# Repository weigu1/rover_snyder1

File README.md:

# Creative-lab space mining rover: Snyder 1

## Some infos

The rover is WLAN controlled by a computer or phone. The new  version uses websockets to controll the rover using sliders.
The rover was developed by Jean Daubenfeld and myself for the [creative-lab](http://creative-lab.lu) and was build 35 times on 2 Luxemburgish Makerfest.

## All infos ESP8266 version : <http://www.weigu.lu/microcontroller/rover/index.html>
## All infos ESP32 version : <http://weigu.lu/tutorials/electronics/01_rover/index.html>

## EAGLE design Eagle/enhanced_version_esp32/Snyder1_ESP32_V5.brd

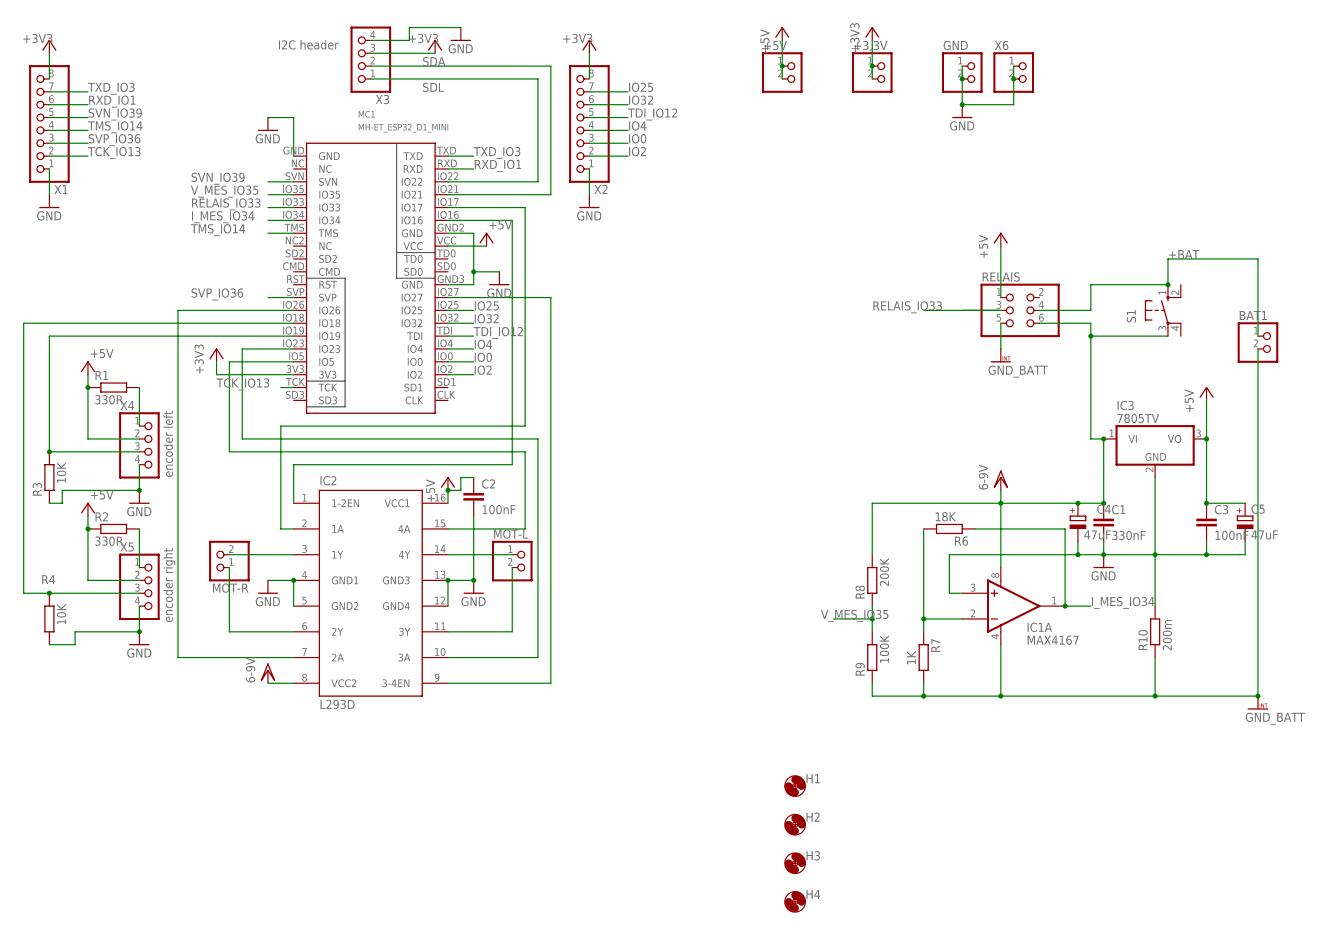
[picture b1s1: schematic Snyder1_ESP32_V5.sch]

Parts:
+3,3V, +5V: PINHD-1X2; 1X02
BAT1: PINHD-1X2; 1X02
C1: 330nF; C050-025X075
C2, C3: 100nF; C050-025X075
C4, C5: 47uF; E2,5-5
GND: PINHD-1X2; 1X02
H1, H2, H3, H4: MOUNT-HOLE3.2; 3,2
IC1: MAX4167; DIL08
IC2: L293D; DIL16
IC3: 7805TV; TO220V
MC1: MH-ET_ESP32_D1_MINI
MOT-L: PINHD-1X2; 1X02
MOT-R: PINHD-1X2; 1X02
R1, R2: 330R; 0207/10
R3, R4: 10K; 0207/10
R6: 18K; 0207/10
R7: 1K; 0207/10
R8: 200K; 0207/10
R9: 100K; 0207/10
R10: 200m; 0411/15
RELAIS: PINHD-2X3; 2X03
S1: 10-XX; B3F-10XX
X1, X2: PINHD-1X8; 1X08
X3: I2C header; 1X04
X4: encoder left; 1X04
X5: encoder right; 1X04
X6: PINHD-1X2; 1X02

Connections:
6-9V: C1.1, C4.+, IC1.8 (V+), IC2.8 (VCC2), IC3.1 (VI), R8.2, RELAIS.6, S1.3
+3V3: +3,3V.1, +3,3V.2, MC1.3V3, X1.8, X2.8, X3.3
+5V: +5V.1, +5V.2, C2.1, C3.1, C5.+, IC2.16 (VCC1), IC3.3 (VO), MC1.VCC, R1.1, R2.1, RELAIS.1, X4.2, X5.2
+BAT: BAT1.1, RELAIS.4, S1.1 (S)
GND: C1.2, C2.2, C3.2, C4.-, C5.-, GND.1, GND.2, IC1.3 (+IN), IC2.4 (GND1), IC2.5 (GND2), IC2.12 (GND4), IC2.13 (GND3), IC3.2 (GND), MC1.GND, MC1.GND2 (GND), MC1.GND3 (GND), R3.1, R4.1, R10.2, X1.1, X2.1, X3.4, X4.4, X5.4, X6.1, X6.2
GNDINT: BAT1.2, IC1.4 (V-), R7.2, R9.1, R10.1, RELAIS.5
IO0: MC1.IO0, X2.3
IO2: MC1.IO2, X2.2
IO4: MC1.IO4, X2.4
IO25: MC1.IO25, X2.7
IO32: MC1.IO32, X2.6
I_MES_IO34: IC1.1 (OUT), MC1.IO34, R6.1
unnamed: IC2.3 (1Y), MOT-R.2
unnamed: IC2.6 (2Y), MOT-R.1
unnamed: IC2.14 (4Y), MOT-L.1
unnamed: IC2.11 (3Y), MOT-L.2
unnamed: IC2.10 (3A), MC1.IO23
unnamed: IC2.15 (4A), MC1.IO5
unnamed: R2.2, X5.1
unnamed: R1.2, X4.1
unnamed: IC2.2 (1A), MC1.IO17
unnamed: MC1.IO19, R3.2, X4.3
unnamed: MC1.IO18, R4.2, X5.3
unnamed: IC2.7 (2A), MC1.IO26
unnamed: IC1.2 (-IN), R6.2, R7.1
unnamed: IC2.1 (1-2EN), MC1.IO16
unnamed: IC2.9 (3-4EN), MC1.IO27
RELAIS_IO33: MC1.IO33, RELAIS.3
RXD_IO1: MC1.RXD, X1.6
SDA: MC1.IO21, X3.2
SDL: MC1.IO22, X3.1
SVN_IO39: MC1.SVN, X1.5
SVP_IO36: MC1.SVP, X1.3
TCK_IO13: MC1.TCK, X1.2
TDI_IO12: MC1.TDI, X2.5
TMS_IO14: MC1.TMS, X1.4
TXD_IO3: MC1.TXD, X1.7
V_MES_IO35: MC1.IO35, R8.1, R9.2

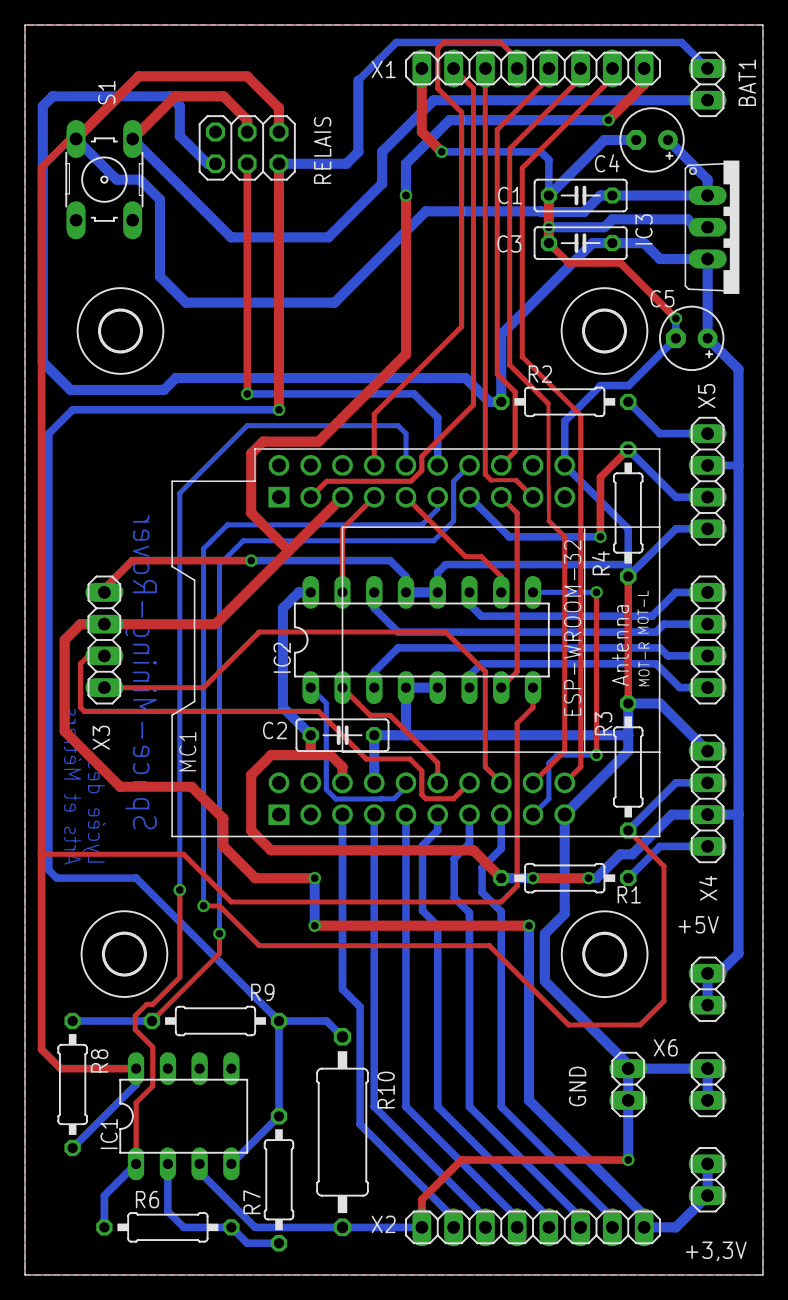
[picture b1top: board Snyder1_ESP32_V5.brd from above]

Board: 2 copper layers, 59.0 x 100.0 mm, 36 parts (0 on the bottom side), 38 nets.

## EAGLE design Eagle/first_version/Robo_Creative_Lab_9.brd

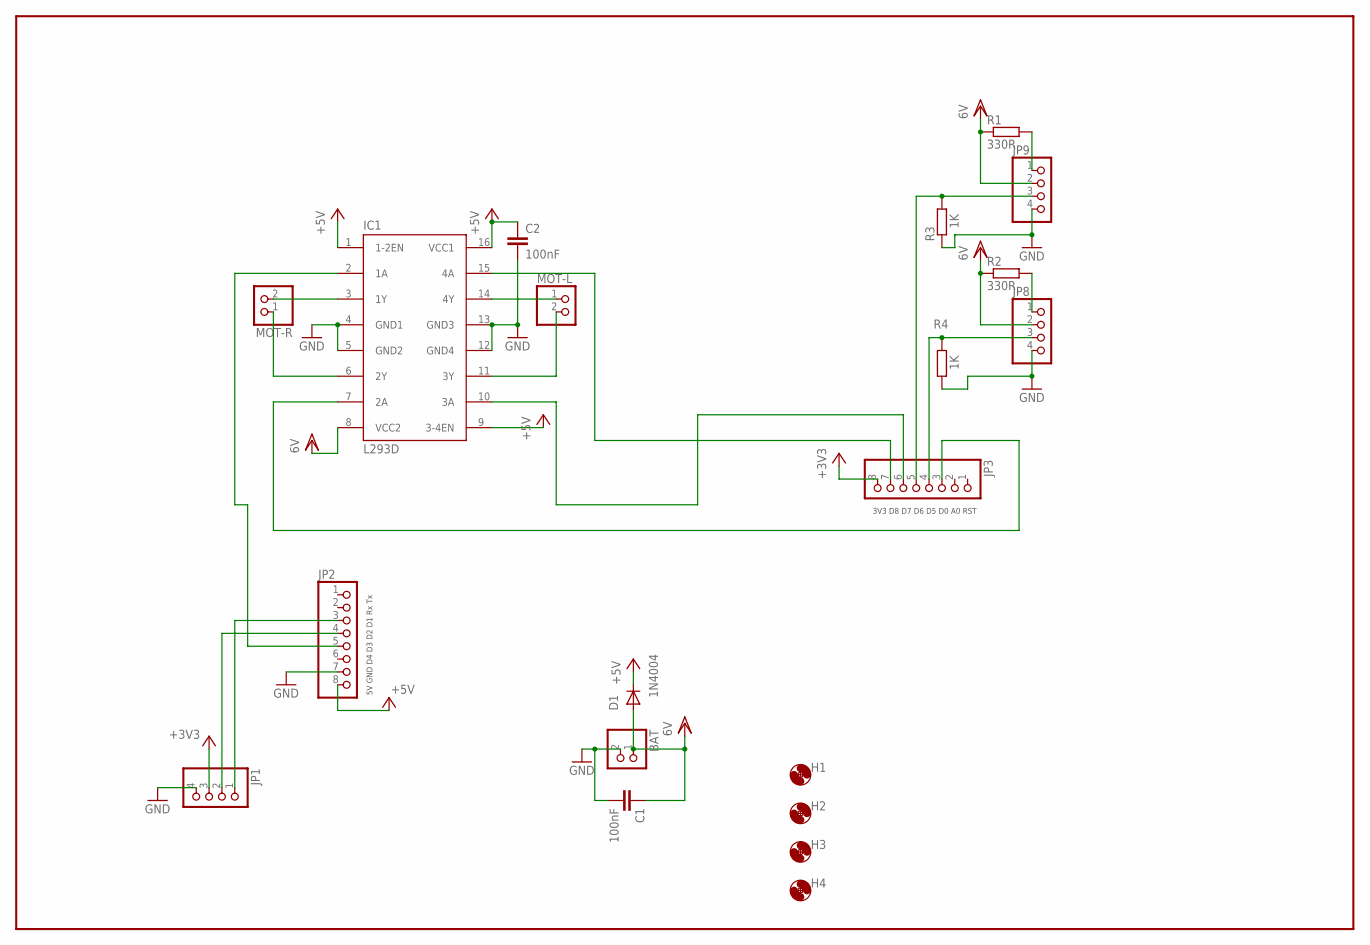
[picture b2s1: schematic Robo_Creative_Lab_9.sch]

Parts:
BAT: PINHD-1X2; 1X02
C1, C2: 100nF; C050-025X075
D1: 1N4004; DO41-10
H1, H2, H3, H4: MOUNT-HOLE3.2; 3,2
IC1: L293D; DIL16
JP1, JP8, JP9: PINHD-1X4; 1X04
JP2, JP3: PINHD-1X8; 1X08
MOT-L: PINHD-1X2; 1X02
MOT-R: PINHD-1X2; 1X02
R1, R2: 330R; 0207/10
R3, R4: 1K; 0207/10

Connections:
+3V3: JP1.3, JP3.8
+5V: C2.1, D1.C, IC1.1 (1-2EN), IC1.9 (3-4EN), IC1.16 (VCC1), JP2.8
GND: BAT.2, C1.2, C2.2, IC1.4 (GND1), IC1.5 (GND2), IC1.12 (GND4), IC1.13 (GND3), JP1.4, JP2.7, JP8.4, JP9.4, R3.1, R4.1
unnamed: IC1.3 (1Y), MOT-R.2
unnamed: IC1.6 (2Y), MOT-R.1
unnamed: IC1.14 (4Y), MOT-L.1
unnamed: IC1.11 (3Y), MOT-L.2
unnamed: IC1.7 (2A), JP3.3
unnamed: IC1.10 (3A), JP3.6
unnamed: IC1.15 (4A), JP3.7
unnamed: JP8.1, R2.2
unnamed: JP9.1, R1.2
unnamed: IC1.2 (1A), JP2.5
unnamed: JP3.5, JP9.3, R3.2
unnamed: JP3.4, JP8.3, R4.2
unnamed: JP1.1, JP2.3
unnamed: JP1.2, JP2.4
VDD: BAT.1, C1.1, D1.A, IC1.8 (VCC2), JP8.2, JP9.2, R1.1, R2.1

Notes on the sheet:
5V GND D4 D3 D2 D1 Rx Tx
3V3 D8 D7 D6 D5 D0 A0 RST

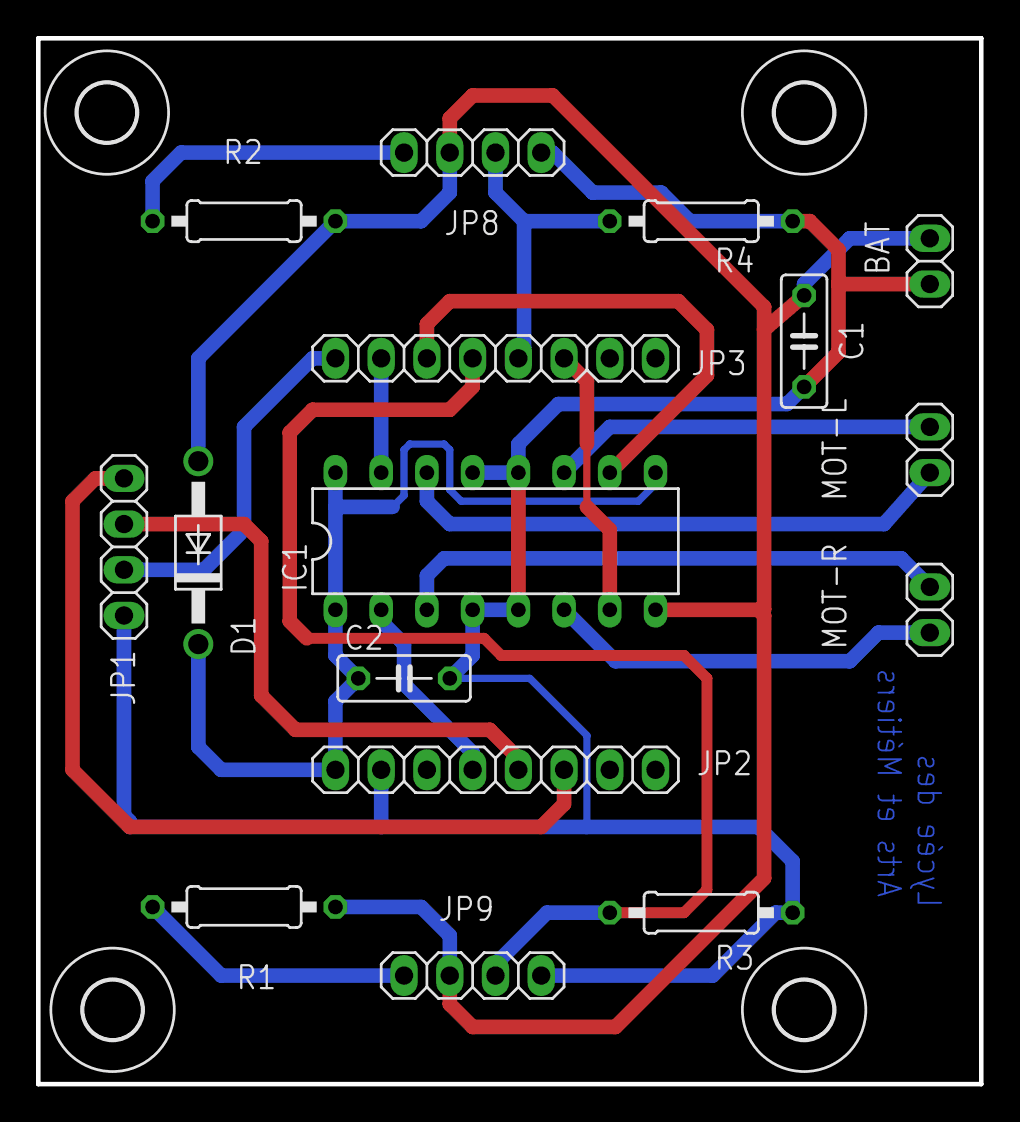
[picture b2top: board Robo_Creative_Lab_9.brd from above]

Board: 2 copper layers, 52.4 x 58.1 mm, 20 parts (0 on the bottom side), 18 nets.

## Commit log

2021-11-04 changed slider position
2021-11-09 pwm range error (esp8266, core>=3.0) corrected
2022-02-09 added zip file for Arduino folder
2023-01-09 add eagle files
